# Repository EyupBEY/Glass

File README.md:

# The Most Quality ESP32-S3 Board Ever Made

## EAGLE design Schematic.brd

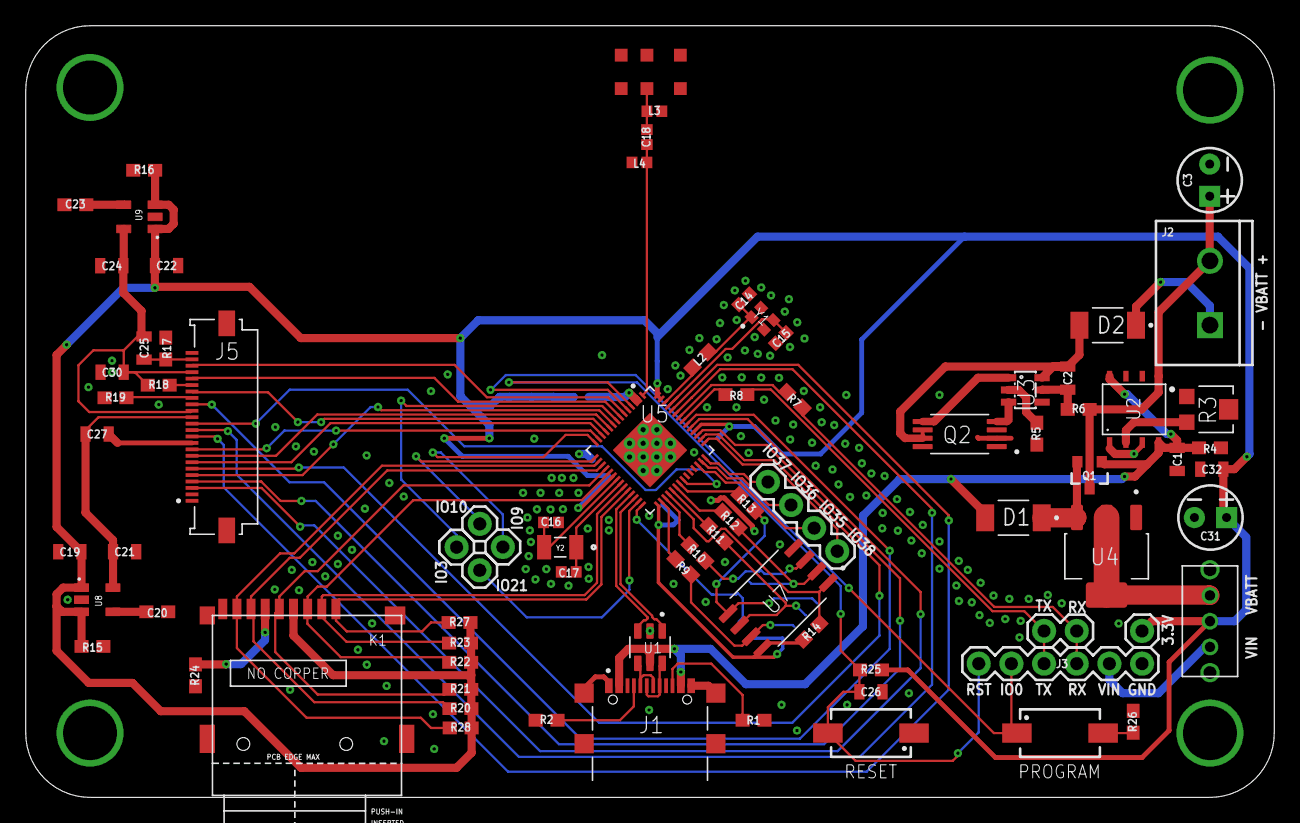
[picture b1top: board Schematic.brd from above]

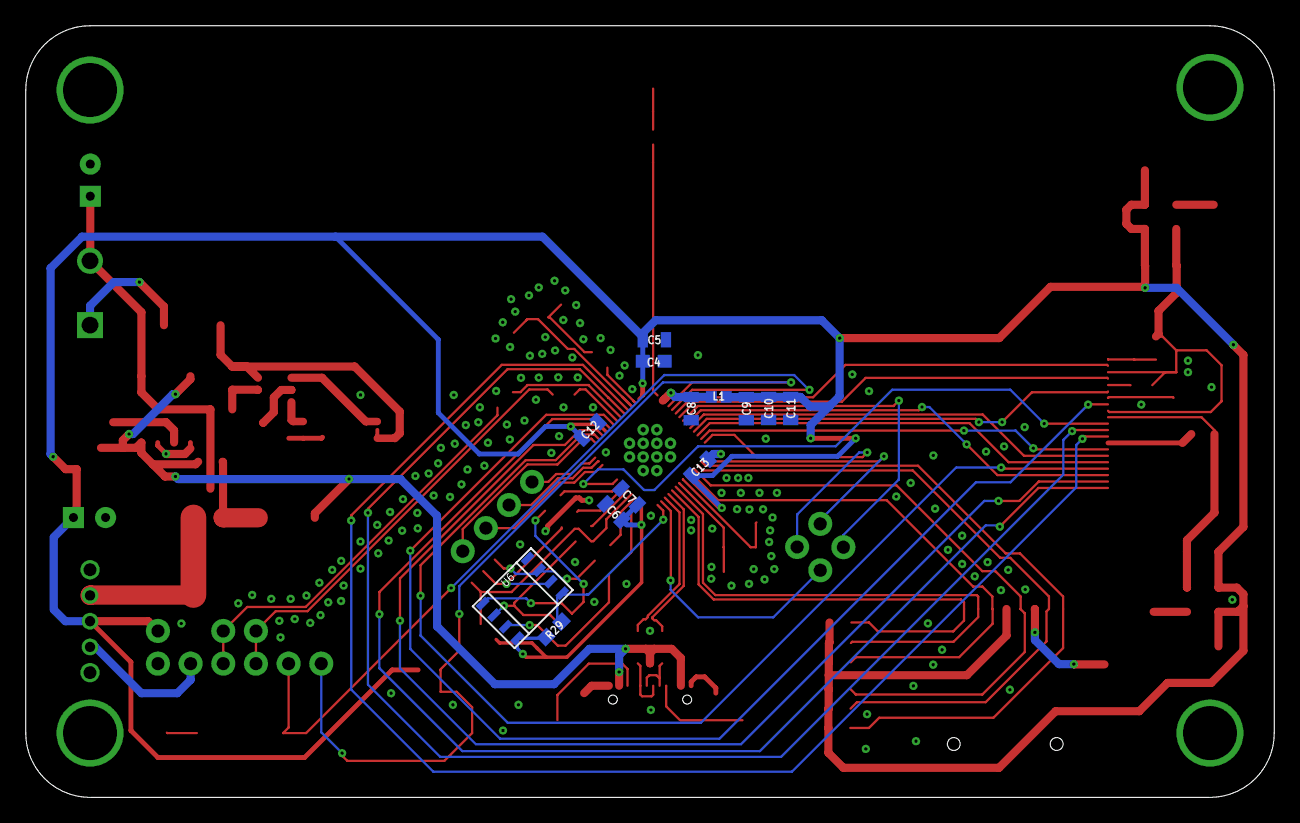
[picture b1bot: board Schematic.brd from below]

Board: 2 copper layers, 97.1 x 60.0 mm, 92 parts (13 on the bottom side), 84 nets.

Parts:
ANT1: SR4W035
C1, C2, C6, C8, C9, C12, C13, C26, C27, C30, C32: 0.1μF; 0805
C3, C31: 10uF; CPOL-RADIAL-2.5MM-5MM
C4: 0.01μF; 0603
C5, C7, C10, C25: 1μF; 0805
C11: 10μF; 0805
C14, C15, C16, C17: 16pF; 0402
C18: 1.5pF; 0402
C19, C21, C22, C24: 1μF/X7R; 0805
C20, C23: 22nF; 0603
D1, D2: PMEG6030EVPX; DIO_PMEG6030EVPX
J1: GSB1C41110SSHR; AMPHENOL_GSB1C41110SSHR
J2: TB002-500-02BE; SCREWTERMINAL-5MM-2
J3: 1X06
J4: 1X04
J5: 5051102491; MOLEX_5051102491
J6, J7, J9: 1X02
J8: 1X01
K1: 112J-TDAR-R01
L1: 2nH/±0.1nH; 0402
L2: 24nH; 0603
L3: 2nH; 0402
L4: (NC); 0402
PROGRAM: 434121043816
Q1: AO3421E; SOT23-3
Q2: FS8205A; SOP65P640X120-8N
R1, R2, R18, R19: 5.1K; 0603
R3: TC33X-2-103E; TRIM_TC33X-2-103E
R4, R15, R16: 100K; 0603
R5: 1K; 0603
R6: 100; 0603
R7, R9, R10, R11, R12, R13, R17, R24: 0; 0603
R8: 499; 0603
R14, R29: 10K(NC); 0603
R20, R21, R22, R23, R25, R26, R27, R28: 10K; 0603
RESET: 434121043816
SW1: 1825232-1
U1: USBLC6-2SC6; SOT95P280X145-6N
U2: TP4056; SOT23-8
U3: DW01A; SOT23-6
U4: LDL1117S33R; SOT230P700X180-4N
U5: ESP32-S3R8; IC_ESP32-S3
U6: SOP
U7: W25Q128JVSIQ; SOIC127P790X216-8N
U8: RT9193-12GB; SOT94P279X129-5N
U9: RT9193-28GB; SOT94P279X129-5N
Y1: ECS-400-10-37B2-CKM-TR; XTAL_ECS-400-10-37B2-CKM-TR
Y2: ECS-.327-6-34QCS-TR; XTAL_ECS-.327-6-34QCS-TR

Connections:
1.1V: C21.2, C27.2, J5.14, U8.5
2.8V: C24.2, C25.2, C30.2, J5.15, J5.21, R18.1, U9.5
3.3V: C4.2, C5.2, C9.2, C10.2, C11.2, C12.2, C13.2, C19.2, C22.2, C31.1, C32.2, J8.1, K1.4, L1.2, R15.2, R16.2, R20.2, R21.2, R22.2, R23.2, R25.2, R27.2, R28.2, SW1.2, U5.20, U5.46, U5.55, U5.56, U8.1, U8.3, U9.1, U9.3
CHIP_PU: C26.2, J3.6, R25.1, RESET.2, U5.4
GND: ANT1.3, ANT1.4, ANT1.6, C1.1, C3.2, C4.1, C5.1, C6.1, C7.1, C8.1, C9.1, C10.1, C11.1, C12.1, C13.1, C14.1, C15.1, C16.2, C17.2, C19.1, C20.1, C21.1, C22.1, C23.1, C24.1, C26.1, C27.1, C30.1, C31.2, C32.1, J1.A1_B12, J1.B1_A12, J1.SH1, J1.SH2, J1.SH3, J1.SH4, J3.1, J5.10, J5.S1, J5.S2, K1.G, L3.2, L4.2, Q2.2, Q2.3, R1.1, R2.1, R3.2, R4.1, R5.1, R15.1, R16.1, R17.1, R19.1, R24.1, R26.2, RESET.1, SW1.GND, SW1.GND1, U1.2, U2.1, U2.3, U4.1, U5.57, U6.VSS, U7.4, U8.2, U9.2, Y1.2, Y1.4
IO0: J3.5, PROGRAM.1, U5.5
IO1: J5.22, U5.6
IO2: J5.20, U5.7
IO3: J7.2, U5.8
IO4: J5.5, U5.9
IO5: J5.8, U5.10
IO6: J5.18, U5.11
IO7: J5.7, U5.12
IO8: J5.9, U5.13
IO9: J6.1, U5.14
IO10: J6.2, U5.15
IO11: K1.8, R28.1, U5.16
IO12: K1.7, R20.1, U5.17
IO13: K1.5, R21.1, U5.18
IO14: K1.3, R22.1, U5.19
IO17: K1.2, R23.1, U5.23
IO18: K1.1, R27.1, U5.24
IO21: J7.1, U5.27
IO35: J4.2, U5.40
IO36: J4.3, U5.41
IO37: J4.4, U5.42
IO38: J4.1, U5.43
IO45: J5.12, U5.51
IO46: J5.11, U5.52
LNA_IN: C18.1, L4.1, U5.1
MTCK: J5.6, U5.44
MTDI: J5.3, U5.47
MTDO: J5.4, U5.45
MTMS: J5.16, U5.48
unnamed: J1.A7, J1.B7, U1.4
unnamed: Q2.5, U3.1
unnamed: Q2.4, U3.3
unnamed: J1.A5, R2.2
unnamed: R5.2, U3.2
unnamed: J1.B5, R1.2
unnamed: K1.6, R24.2
unnamed: R3.3, U2.2
unnamed: C8.2, L1.1, U5.2, U5.3
unnamed: D2.1, J2.1
unnamed: C2.2, R6.1, U3.5
unnamed: ANT1.2, C18.2, L3.1
unnamed: C14.2, L2.2, Y1.1
unnamed: J1.A6, J1.B6, U1.6
unnamed: C2.1, D2.2, Q2.6, Q2.7, U3.6
unnamed: C20.2, U8.4
unnamed: C23.2, U9.4
unnamed: J5.19, R18.2
unnamed: PROGRAM.2, R26.1
unnamed: R7.2, U5.50
unnamed: R8.2, U5.49
unnamed: C3.1, J2.2, Q1.3, R6.2, U2.5
unnamed: R9.2, U5.30
unnamed: R10.2, U5.31
unnamed: D1.1, Q1.2, U4.3
unnamed: R11.2, U5.33
unnamed: R12.2, U5.34
unnamed: R13.2, U5.35
unnamed: J5.17, R19.2
unnamed: C25.1, J5.23, R17.2
SPICLK: R11.1, U6.SCLK, U7.6
SPICLK_N: J5.13, U5.36
SPICS0: R14.1, U5.32, U7.1
SPICS1: R29.1, U5.28, U6.CE#
SPID: R13.1, U6.SI/SIO[0], U7.5
SPIHD: R9.1, U6.SIO[3], U7.7
SPIQ: R12.1, U6.SO/SIO[1], U7.2
SPIWP: R10.1, U6.SIO[2], U7.3
U0RXD: J3.3, J9.1, R7.1
U0TXD: J3.4, J9.2, R8.1
USB_D_N: U1.3, U5.25
USB_D_P: U1.1, U5.26
VDD_SPI: C6.2, C7.2, R14.2, R29.2, U5.29, U6.VCC, U7.8
VIN: J3.2, SW1.1
V_BATT: SW1.3, U4.2, U4.4
V_USB: C1.2, D1.2, J1.A4_B9, J1.B4_A9, Q1.1, R4.2, U1.5, U2.4, U2.8
XTAL_32K_N: C17.1, U5.22, Y2.1
XTAL_32K_P: C16.1, U5.21, Y2.2
XTAL_N: C15.2, U5.53, Y1.3
XTAL_P: L2.1, U5.54

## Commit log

2024-02-29 very first
2024-02-29 developed
2024-03-03 Rev0
2024-03-05 Rev 1
2024-03-05 Rev1
2024-04-22 first
2024-05-20 Create First Commit
2024-05-20 Create LICENSE
2024-05-24 Create hel
2024-06-28 Rename Schematic.brd to Layout.brd
2024-09-20 Create hr

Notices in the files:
parts and their libraries:
SparkFun-Capacitors: Licensing: Creative Commons ShareAlike 4.0 International - https://creativecommons.org/licenses/by-sa/4.0
